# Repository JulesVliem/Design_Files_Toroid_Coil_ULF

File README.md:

# Supporting Files for the Toroidal RF Volume Coil at ULF MRI

This repository contains supplementary design files for the paper "Design and performance of a Toroidal RF Volume Coil with Intrinsic Electromagnetic Interference Rejection for low-field Portable Halbach-Based MRI Systems" by J. Vliem et al. etc. (currently available as a preprint on arXiv: https://arxiv.org/abs/2505.21745).

## Contents

For the 3D design files you will find SolidWorks part files (`.SLDPRT`), STEP files (`.step`), and STL files (`.stl`) for various CAD software compatibility and 3D printing. The repository is organized into the following folders:

* **`Quadruple Toroid Holder`**: Contains the 3D design files for the toroid holder. 
* **`Quadruple Twist Half`**: Includes 3D printable files for the toroid split into two halves, ideal for users with smaller 3D printers.
* **`Quadruple Twist Whole`**: Provides the complete 3D design files for the full toroid.
* **`PCB Design`**: Contains the KiCad project files for the printed circuit board, along with the corresponding Gerber files for manufacturing.

## Usage

These files are provided to enable replication and further development based on the designs presented in the associated paper. Please refer to the paper for detailed information regarding the design and assembly of these components. Feel free to reach out for any questions!

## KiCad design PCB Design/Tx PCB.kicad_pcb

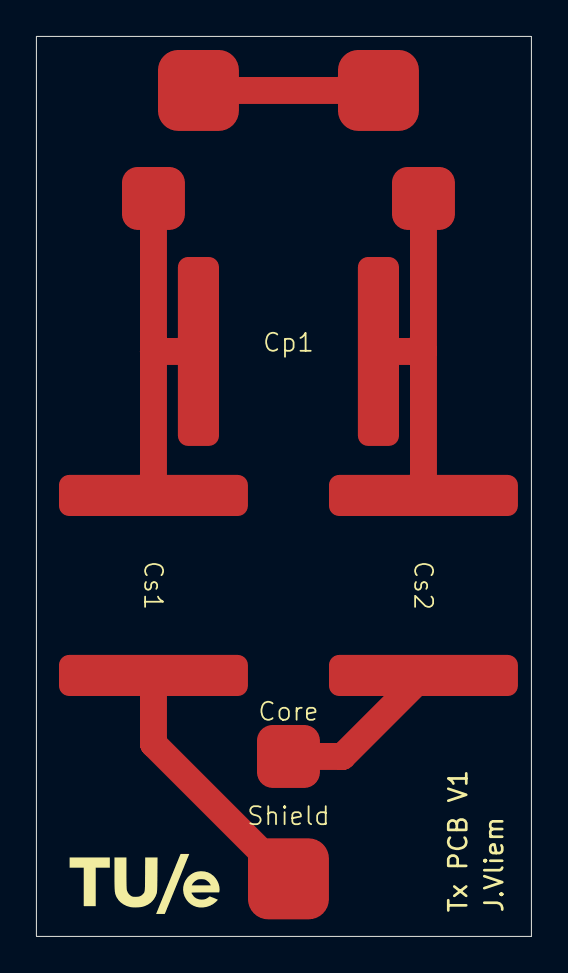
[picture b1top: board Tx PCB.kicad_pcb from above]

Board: 2 copper layers, 27.5 x 50.0 mm, 9 parts (0 on the bottom side), 4 nets.

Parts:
Core: CoaxConnect2
Cp1: C; HighVoltageCapacitor
Cs1, Cs2: C; HighVoltageCapacitor
Shield: CoaxConnect1
Shield#2, Shield#3: CoaxConnect1
U3, U4: CoaxConnect2

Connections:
Earth: Cs1.2, Shield.1 (Coax)
GND: Cp1.1, Cs1.1, U4.1 (Coax)
VDD: Core.1 (Coax), Cs2.2
VDDA: Cp1.2, Cs2.1, U3.1 (Coax)

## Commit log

2025-07-24 Add files via upload
    PCB Files
2025-07-24 Add files via upload
    Holder 3D files
2025-07-24 Add files via upload
    3D files half print toroid
2025-07-24 Add files via upload
    3D files full toroid
